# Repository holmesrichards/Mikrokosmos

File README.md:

# Mikrokosmos
Kosmo format version of Music Thing Modular's Mikrophonie Eurorack synthesizer module (https://github.com/TomWhitwell/Mikrophonie). Almost no change to the circuit (other than the diodes protecting the power supply), but PCB is laid out differently and there is a Kosmo-size front panel inspired by the Eurorack original.

BOM is here: https://github.com/holmesrichards/Mikrokosmos/blob/master/PCB/Mikrokosmos.md

## Build notes

Mostly the build is pretty standard and straightforward.

All PCB mounted parts go on the top side EXCEPT the pot. Don’t be like me and absent mindedly solder it to the same side as everything else. In the completed module the parts other than the pot are on the side of the board facing away from the panel.

The piezo disc mounts to the back of the panel behind the scratch panel, below the screw hole. I used a Scotch double stick adhesive strip and that seemed to work fine.

Solder the red piezo lead to the switch terminal on the Mic In jack. (You’ll probably need to lengthen the piezo wires.) Wire jack grounds to one of the ground terminals on the board and the tip terminals to the Mic In + and Output + terminals. I specified 2 pin Molex headers for the jack connections but on mine I just soldered the wires.

The bottom of the PCB is secured to the panel via the pot. Use a 10 mm M3 spacer and two M3 screws to secure the top of the PCB.

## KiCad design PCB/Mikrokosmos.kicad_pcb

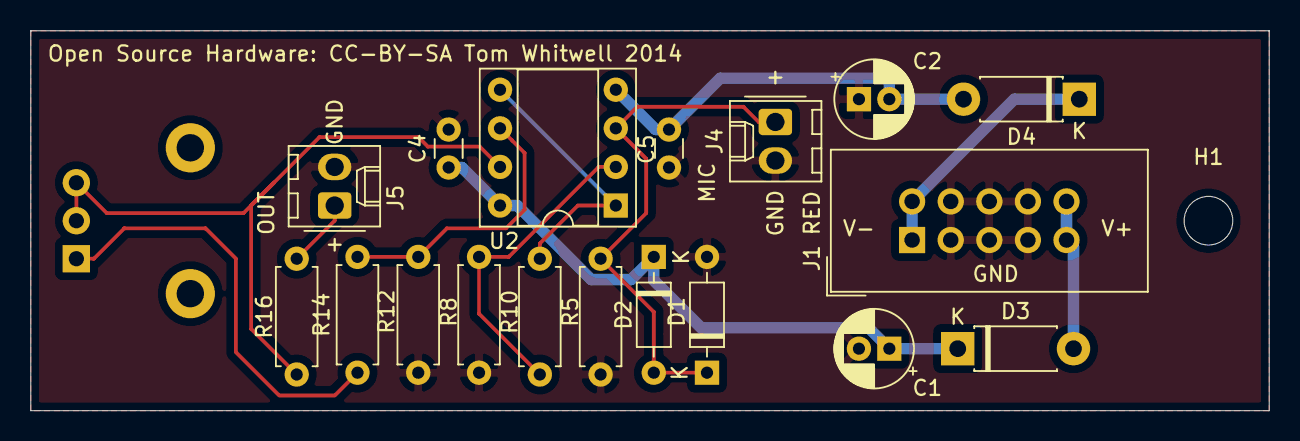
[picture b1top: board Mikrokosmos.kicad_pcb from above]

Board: 2 copper layers, 81.5 x 25.0 mm, 20 parts (1 on the bottom side), 12 nets.

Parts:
C1, C2: 10uF; CP_Radial_D5.0mm_P2.00mm
C4, C5: 0.1uF; C_Disc_D3.0mm_W1.6mm_P2.50mm
D1, D2: 1N4148; D_DO-35_SOD27_P7.62mm_Horizontal
D3, D4: 1N5817; D_DO-41_SOD81_P7.62mm_Horizontal
H1: MountingHole; MountingHole_3.2mm_M3
J1: EURO_PWR_2x5; Eurorack_Power_Header_Shrouded
J4, J5: Molex 2 pin; Molex_KK-254_AE-6410-02A_1x02_P2.54mm_Vertical
R5: 1M; R_Axial_DIN0207_L6.3mm_D2.5mm_P7.62mm_Horizontal
R8: 10k; R_Axial_DIN0207_L6.3mm_D2.5mm_P7.62mm_Horizontal
R10: 56k; R_Axial_DIN0207_L6.3mm_D2.5mm_P7.62mm_Horizontal
R12, R14: 2.2k; R_Axial_DIN0207_L6.3mm_D2.5mm_P7.62mm_Horizontal
R16: 220R; R_Axial_DIN0207_L6.3mm_D2.5mm_P7.62mm_Horizontal
RV1: 50k; Potentiometer_Alpha_RD901F-40-00D_Single_Vertical_CircularH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
U2: TL072; DIP-8_W7.62mm_Socket

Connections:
+12V: C1.1, C4.1, D1.1, D3.1, U2.8
-12V: C2.2, C5.2, D4.2, U2.4
/MIC+: D1.2, D2.1, J4.1, R5.1, U2.3
GND: C1.2, C2.1, C4.2, C5.1, D2.2, J1.3, J1.4, J1.5, J1.6, J1.7, J1.8, J4.2, J5.2, R5.2, R8.2, R12.2
unnamed: D3.2, J1.9, J1.10
unnamed: D4.1, J1.1, J1.2
unnamed: J5.1, R16.1
unnamed: R10.1, U2.1, U2.5
unnamed: R8.1, R10.2, U2.2
unnamed: R12.1, R14.2, U2.6
unnamed: R14.1, RV1.1
unnamed: R16.2, RV1.2, RV1.3, U2.7

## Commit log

2020-03-30 Initial version
2020-03-30 Added my name and email
2020-03-30 add .gitignore
2020-03-30 Initial versions, PCB and Panel
2020-03-30 rm cruft
2020-04-01 Gerbers
2020-04-01 Connect plane to ground via jacks
2020-04-10 Final panel
2020-04-10 Fab layer tweaks
2020-04-11 BOM update
2020-04-11 BOM link
2020-04-11 Build notes
2020-04-11 Images
2020-04-11 Resize images
2020-04-11 Image
2020-04-11 Disc and knob
2020-04-11 Clean up BOM
2020-04-11 test
2020-04-11 test over
2020-04-11 Markdown BOM
2020-04-11 Link to Markdown BOM
2020-04-12 Move global library to local
2020-04-16 Ignore Mikrokosmos_docs.pdf
2020-04-16 Add info on schematic
2020-04-19 Documentation of artwork process
2020-04-19 Clean up old cruft
2020-04-19 Additional files listed
2020-04-27 Front Cu fill
2020-09-01 Gerbers to a folder
2020-10-25 Update .gitignore, Gerbers
2020-11-21 Ignore .svg
2020-11-27 Changes for new Inkscape version
2021-01-02 Inverted panel
2021-01-17 Include lib table files

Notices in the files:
PCB/Mikrokosmos.kicad_pcb:
Open Source Hardware: CC-BY-SA Tom Whitwell 2014
